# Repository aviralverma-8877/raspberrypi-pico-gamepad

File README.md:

# raspberrypi-pico-gamepad
Raspberry Pi Pico based Gamepad

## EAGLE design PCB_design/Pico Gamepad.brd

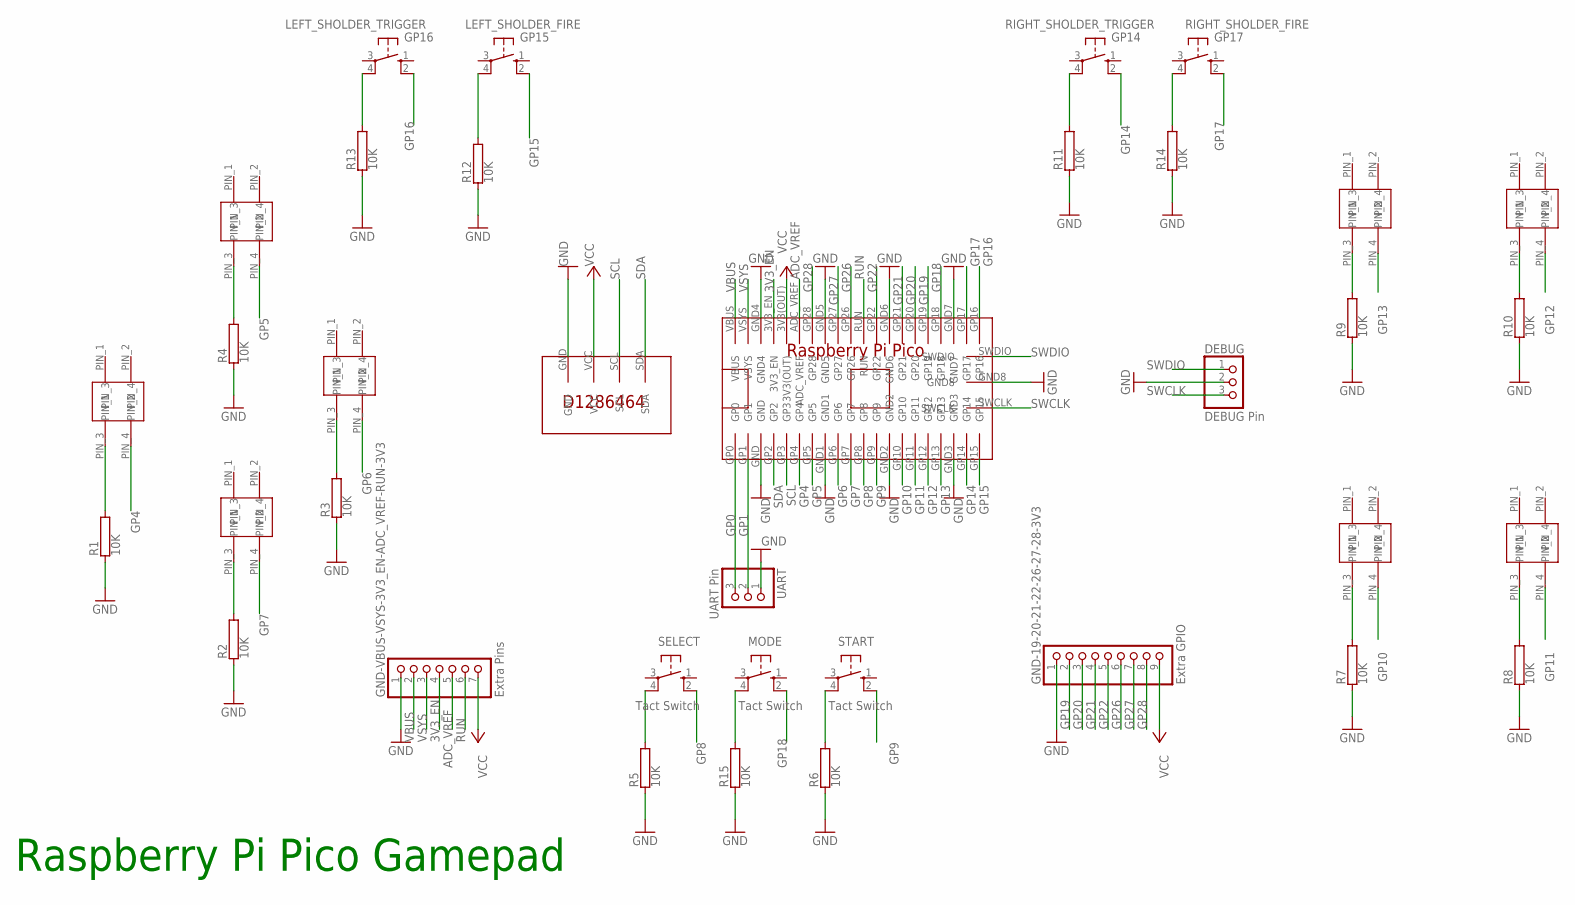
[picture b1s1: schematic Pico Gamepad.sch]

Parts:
A: GAMEPAD_BTN
B: GAMEPAD_BTN
DEBUG: DEBUG Pin; 1X03
DOWN: GAMEPAD_BTN
GND-19-20-21-22-26-27-28-3V3: Extra GPIO; 1X09
GND-VBUS-VSYS-3V3_EN-ADC_VREF-RUN-3V3: Extra Pins; 1X07
LEFT: GAMEPAD_BTN
LEFT_SHOLDER_FIRE: GP15; B3F-10XX
LEFT_SHOLDER_TRIGGER: GP16; B3F-10XX
MODE: Tact Switch; B3F-10XX
R1, R2, R3, R4, R5, R6, R7, R8, R9, R10, R11, R12, R13, R14, R15: 10K; RS1/8
RIGHT: GAMEPAD_BTN
RIGHT_SHOLDER_FIRE: GP17; B3F-10XX
RIGHT_SHOLDER_TRIGGER: GP14; B3F-10XX
SELECT: Tact Switch; B3F-10XX
START: Tact Switch; B3F-10XX
U$1: RASPBERRYPIPICO
U$2: OLED_DISPLAY
UART: UART Pin; 1X03
UP: GAMEPAD_BTN
X: GAMEPAD_BTN
Y: GAMEPAD_BTN

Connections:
3V3_EN: GND-VBUS-VSYS-3V3_EN-ADC_VREF-RUN-3V3.4, U$1.3V3_EN
ADC_VREF: GND-VBUS-VSYS-3V3_EN-ADC_VREF-RUN-3V3.5, U$1.ADC_VREF
GND: DEBUG.2, GND-19-20-21-22-26-27-28-3V3.1, GND-VBUS-VSYS-3V3_EN-ADC_VREF-RUN-3V3.1, R1.1, R2.1, R3.1, R4.1, R5.1, R6.1, R7.1, R8.1, R9.1, R10.1, R11.1, R12.1, R13.1, R14.1, R15.1, U$1.GND, U$1.GND1, U$1.GND2, U$1.GND3, U$1.GND4, U$1.GND5, U$1.GND6, U$1.GND7, U$1.GND8, U$2.GND, UART.1
GP0: U$1.GP0, UART.3
GP1: U$1.GP1, UART.2
GP4: LEFT.PIN_4, U$1.GP4
GP5: U$1.GP5, UP.PIN_4
GP6: RIGHT.PIN_4, U$1.GP6
GP7: DOWN.PIN_4, U$1.GP7
GP8: SELECT.2 (S1), U$1.GP8
GP9: START.2 (S1), U$1.GP9
GP10: A.PIN_4, U$1.GP10
GP11: B.PIN_4, U$1.GP11
GP12: U$1.GP12, Y.PIN_4
GP13: U$1.GP13, X.PIN_4
GP14: RIGHT_SHOLDER_TRIGGER.2 (S1), U$1.GP14
GP15: LEFT_SHOLDER_FIRE.2 (S1), U$1.GP15
GP16: LEFT_SHOLDER_TRIGGER.2 (S1), U$1.GP16
GP17: RIGHT_SHOLDER_FIRE.2 (S1), U$1.GP17
GP18: MODE.2 (S1), U$1.GP18
GP19: GND-19-20-21-22-26-27-28-3V3.2, U$1.GP19
GP20: GND-19-20-21-22-26-27-28-3V3.3, U$1.GP20
GP21: GND-19-20-21-22-26-27-28-3V3.4, U$1.GP21
GP22: GND-19-20-21-22-26-27-28-3V3.5, U$1.GP22
GP26: GND-19-20-21-22-26-27-28-3V3.6, U$1.GP26
GP27: GND-19-20-21-22-26-27-28-3V3.7, U$1.GP27
GP28: GND-19-20-21-22-26-27-28-3V3.8, U$1.GP28
unnamed: R9.2, X.PIN_3
unnamed: R10.2, Y.PIN_3
unnamed: R11.2, RIGHT_SHOLDER_TRIGGER.4 (P1)
unnamed: LEFT_SHOLDER_FIRE.4 (P1), R12.2
unnamed: R4.2, UP.PIN_3
unnamed: LEFT.PIN_3, R1.2
unnamed: DOWN.PIN_3, R2.2
unnamed: R3.2, RIGHT.PIN_3
unnamed: MODE.4 (P1), R15.2
unnamed: R5.2, SELECT.4 (P1)
unnamed: R6.2, START.4 (P1)
unnamed: A.PIN_3, R7.2
unnamed: B.PIN_3, R8.2
unnamed: LEFT_SHOLDER_TRIGGER.4 (P1), R13.2
unnamed: R14.2, RIGHT_SHOLDER_FIRE.4 (P1)
RUN: GND-VBUS-VSYS-3V3_EN-ADC_VREF-RUN-3V3.6, U$1.RUN
SCL: U$1.GP3, U$2.SCL
SDA: U$1.GP2, U$2.SDA
SWCLK: DEBUG.3, U$1.SWCLK
SWDIO: DEBUG.1, U$1.SWDIO
VBUS: GND-VBUS-VSYS-3V3_EN-ADC_VREF-RUN-3V3.2, U$1.VBUS
VCC: GND-19-20-21-22-26-27-28-3V3.9, GND-VBUS-VSYS-3V3_EN-ADC_VREF-RUN-3V3.7, U$1.3V3(OUT), U$2.VCC
VSYS: GND-VBUS-VSYS-3V3_EN-ADC_VREF-RUN-3V3.3, U$1.VSYS

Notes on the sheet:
Raspberry Pi Pico Gamepad

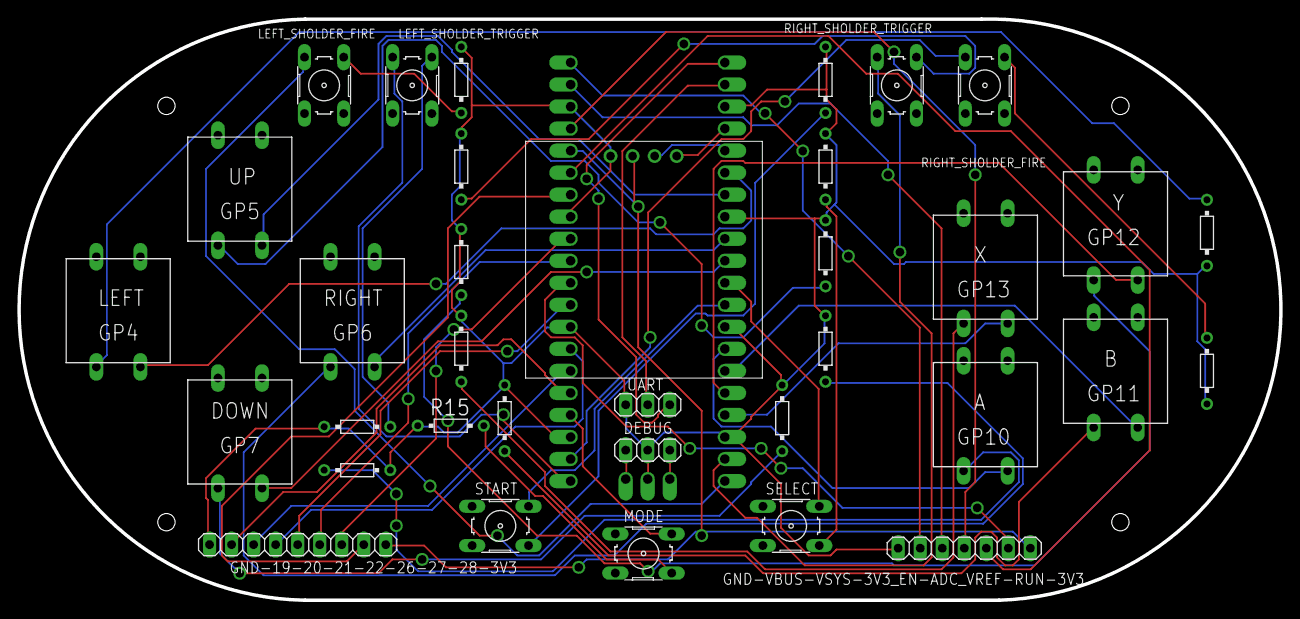
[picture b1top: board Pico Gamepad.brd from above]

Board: 2 copper layers, 145.5 x 67.0 mm, 36 parts (1 on the bottom side), 50 nets.

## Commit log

2021-04-22 Gamepad Firmware Added
2021-04-22 OLED Support Added
2021-04-22 Media Control Added
2021-04-22 OLED Fix
2021-04-22 Welcome Msg Edit
2021-04-23 Trademark Added
2021-04-26 Sleep Time adjusted for Volume Control
2021-04-26 PCB Design Added
2021-06-02 3D Print File added
2021-11-25 Circuit Python added
